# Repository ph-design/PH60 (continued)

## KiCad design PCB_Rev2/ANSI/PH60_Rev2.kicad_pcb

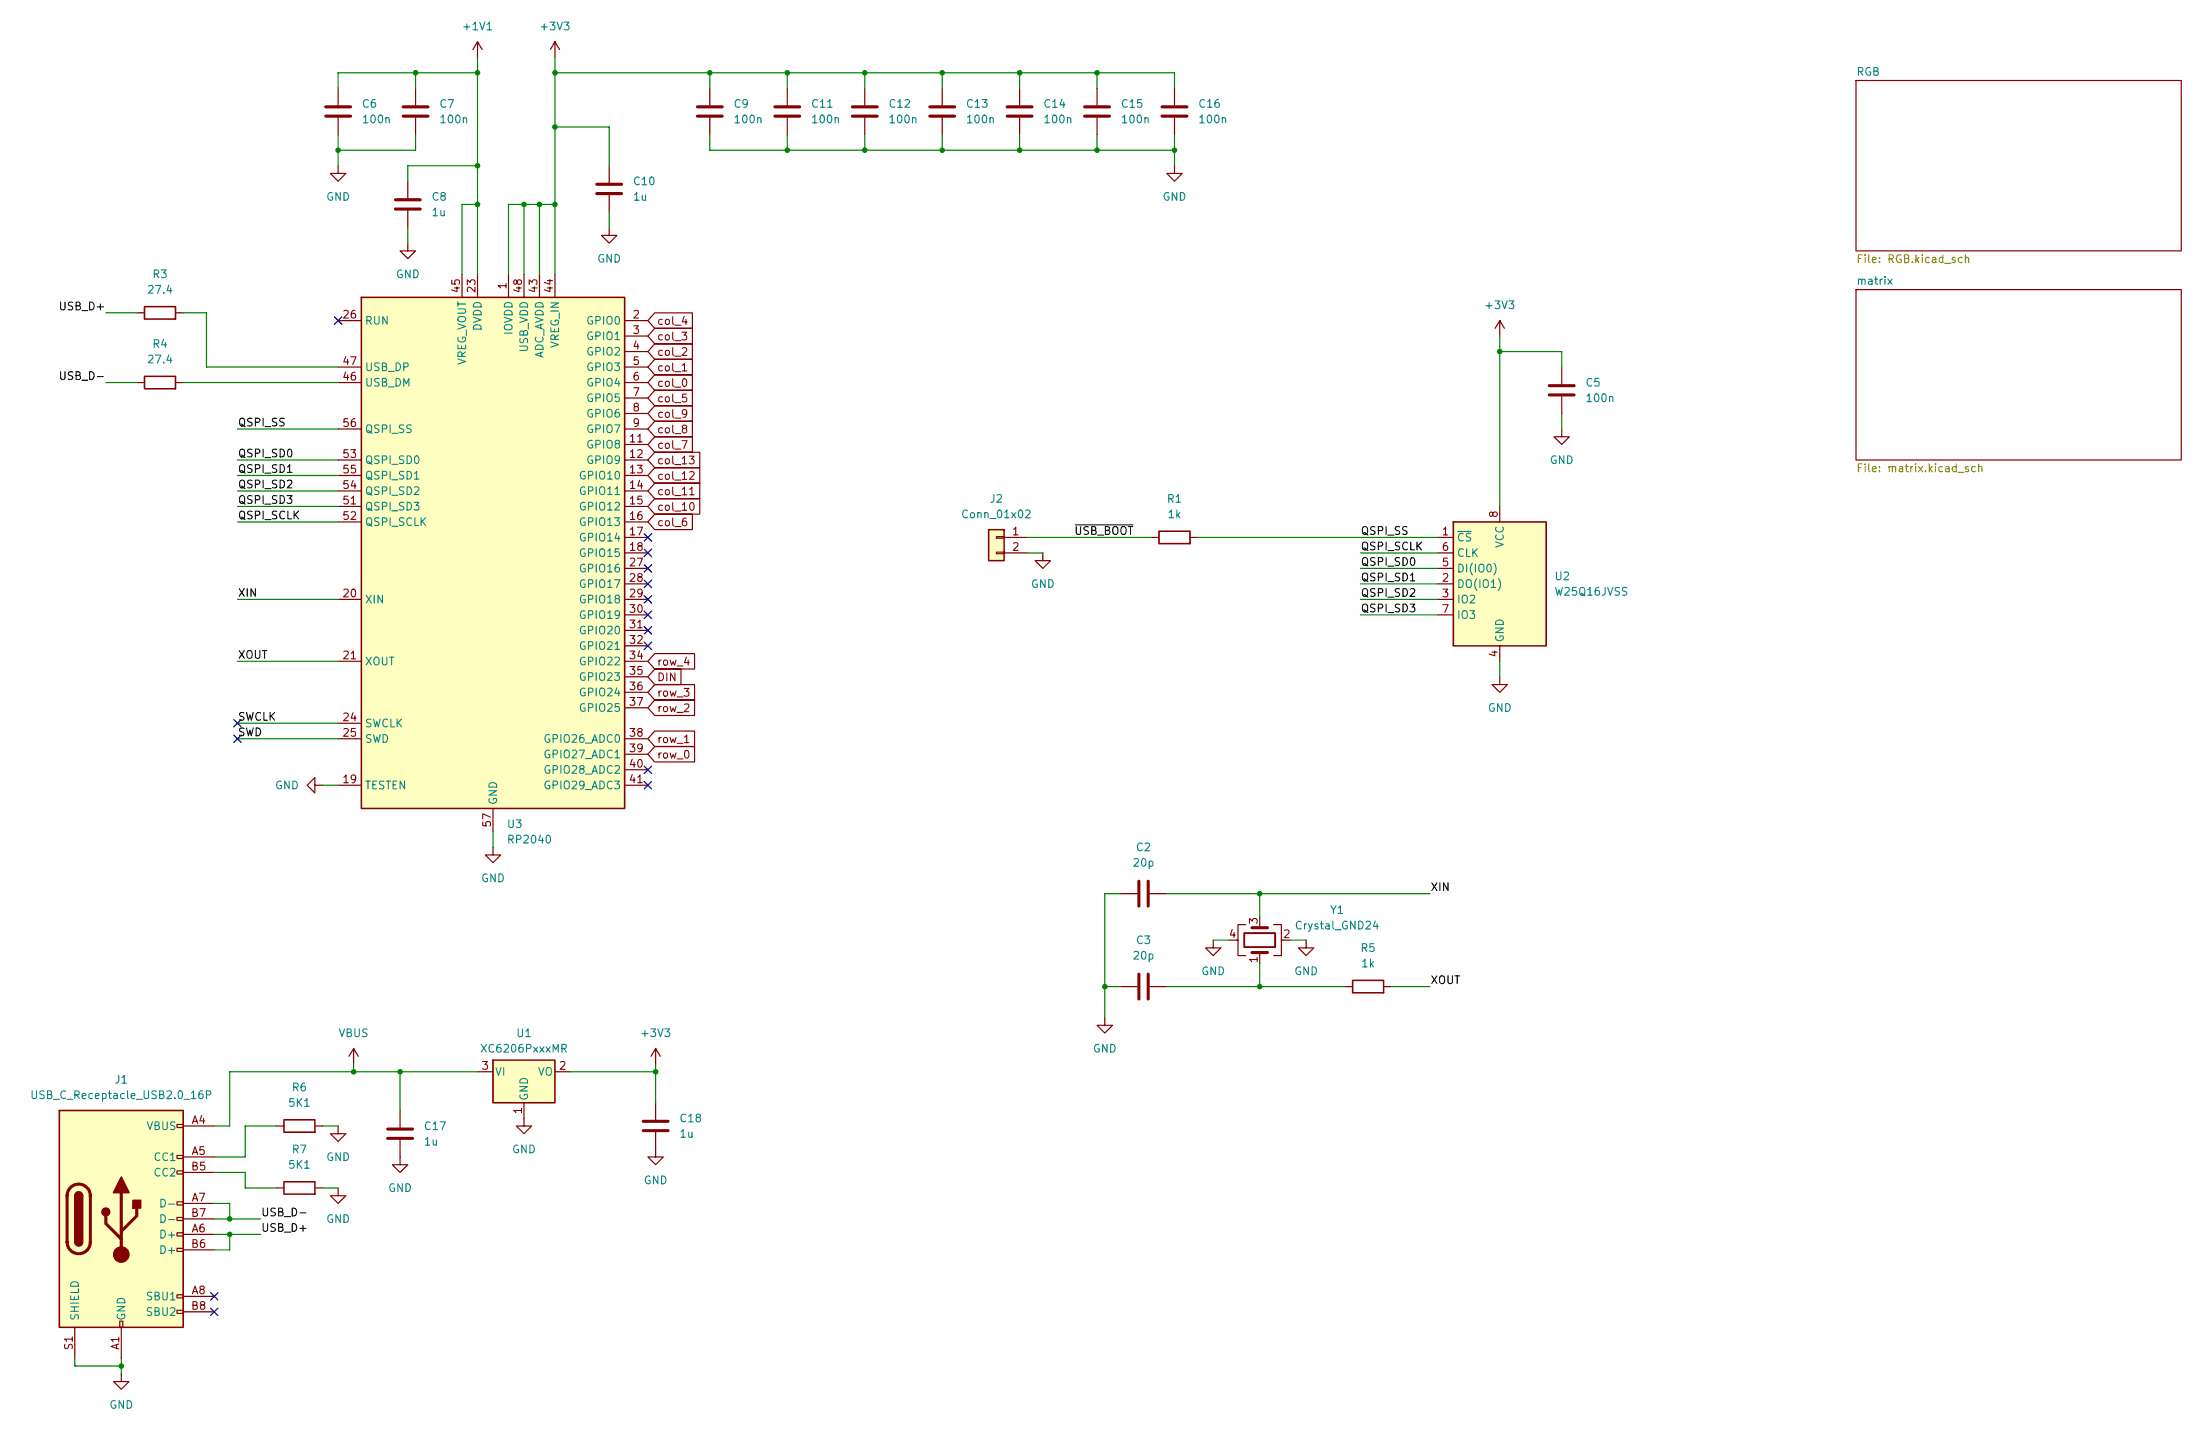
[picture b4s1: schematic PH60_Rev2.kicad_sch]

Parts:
C2, C3: 20p; C_0402_1005Metric
C5, C6, C7, C9, C11, C12, C13, C14, C15, C16: 100n; C_0402_1005Metric
C8, C10, C17, C18: 1u; C_0402_1005Metric
J1: USB_C_Receptacle_USB2.0_16P; USB_C_Receptacle_GCT_USB4105-xx-A_16P_TopMnt_Horizontal
J2: Conn_01x02; PinHeader_1x02_P2.54mm_Vertical
R1, R5: 1k; R_0402_1005Metric
R3, R4: 27.4; R_0402_1005Metric
R6, R7: 5K1; R_0402_1005Metric
U1: XC6206PxxxMR; SOT-23-3
U2: W25Q16JVSS; Winbond_USON-8-1EP_3x2mm_P0.5mm_EP0.2x1.6mm
U3: RP2040; QFN-56-1EP_7x7mm_P0.4mm_EP3.2x3.2mm_ThermalVias
Y1: Crystal_GND24; Crystal_SMD_3225-4Pin_3.2x2.5mm

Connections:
+1V1: C6.1, C7.1, C8.1, U3.23 (DVDD), U3.45 (VREG_VOUT), U3.50 (DVDD)
+3V3: C5.1, C9.1, C10.1, C11.1, C12.1, C13.1, C14.1, C15.1, C16.1, C18.1, U1.2 (VO), U2.8 (VCC), U3.1 (IOVDD), U3.10 (IOVDD), U3.22 (IOVDD), U3.33 (IOVDD), U3.42 (IOVDD), U3.43 (ADC_AVDD), U3.44 (VREG_IN), U3.48 (USB_VDD), U3.49 (IOVDD)
/QSPI_SCLK: U2.6 (CLK), U3.52 (QSPI_SCLK)
/QSPI_SD0: U2.5 (DI(IO0)), U3.53 (QSPI_SD0)
/QSPI_SD1: U2.2 (DO(IO1)), U3.55 (QSPI_SD1)
/QSPI_SD2: U2.3 (IO2), U3.54 (QSPI_SD2)
/QSPI_SD3: U2.7 (IO3), U3.51 (QSPI_SD3)
/QSPI_SS: R1.2, U2.1 (~CS), U3.56 (QSPI_SS)
/SWCLK: U3.24 (SWCLK)
/SWD: U3.25 (SWD)
/USB_D+: J1.A6 (D+), J1.B6 (D+), R3.1
/USB_D-: J1.A7 (D-), J1.B7 (D-), R4.1
/XIN: C2.1, U3.20 (XIN), Y1.3
/XOUT: R5.2, U3.21 (XOUT)
/~USB_BOOT: J2.1, R1.1
DIN: U3.35 (GPIO23); also elsewhere on the board
GND: C2.2, C3.2, C5.2, C6.2, C7.2, C8.2, C9.2, C10.2, C11.2, C12.2, C13.2, C14.2, C15.2, C16.2, C17.2, C18.2, J1.A1 (GND), J1.A12 (GND), J1.B1 (GND), J1.B12 (GND), J1.S1 (SHIELD), J2.2, R6.2, R7.2, U1.1 (GND), U2.4 (GND), U3.19 (TESTEN), U3.57 (GND), Y1.2, Y1.4; also elsewhere on the board
unnamed: C3.1, R5.1, Y1.1
unnamed: J1.A5 (CC1), R6.1
unnamed: J1.B5 (CC2), R7.1
unnamed: R4.2, U3.46 (USB_DM)
unnamed: R3.2, U3.47 (USB_DP)
VBUS: C17.1, J1.A4 (VBUS), J1.A9 (VBUS), J1.B4 (VBUS), J1.B9 (VBUS), U1.3 (VI); also elsewhere on the board
col_0: U3.6 (GPIO4); also elsewhere on the board
col_1: U3.5 (GPIO3); also elsewhere on the board
col_2: U3.4 (GPIO2); also elsewhere on the board
col_3: U3.3 (GPIO1); also elsewhere on the board
col_4: U3.2 (GPIO0); also elsewhere on the board
col_5: U3.7 (GPIO5); also elsewhere on the board
col_6: U3.16 (GPIO13); also elsewhere on the board
col_7: U3.11 (GPIO8); also elsewhere on the board
col_8: U3.9 (GPIO7); also elsewhere on the board
col_9: U3.8 (GPIO6); also elsewhere on the board
col_10: U3.15 (GPIO12); also elsewhere on the board
col_11: U3.14 (GPIO11); also elsewhere on the board
col_12: U3.13 (GPIO10); also elsewhere on the board
col_13: U3.12 (GPIO9); also elsewhere on the board
row_0: U3.39 (GPIO27_ADC1); also elsewhere on the board
row_3: U3.36 (GPIO24); also elsewhere on the board
row_4: U3.34 (GPIO22); also elsewhere on the board

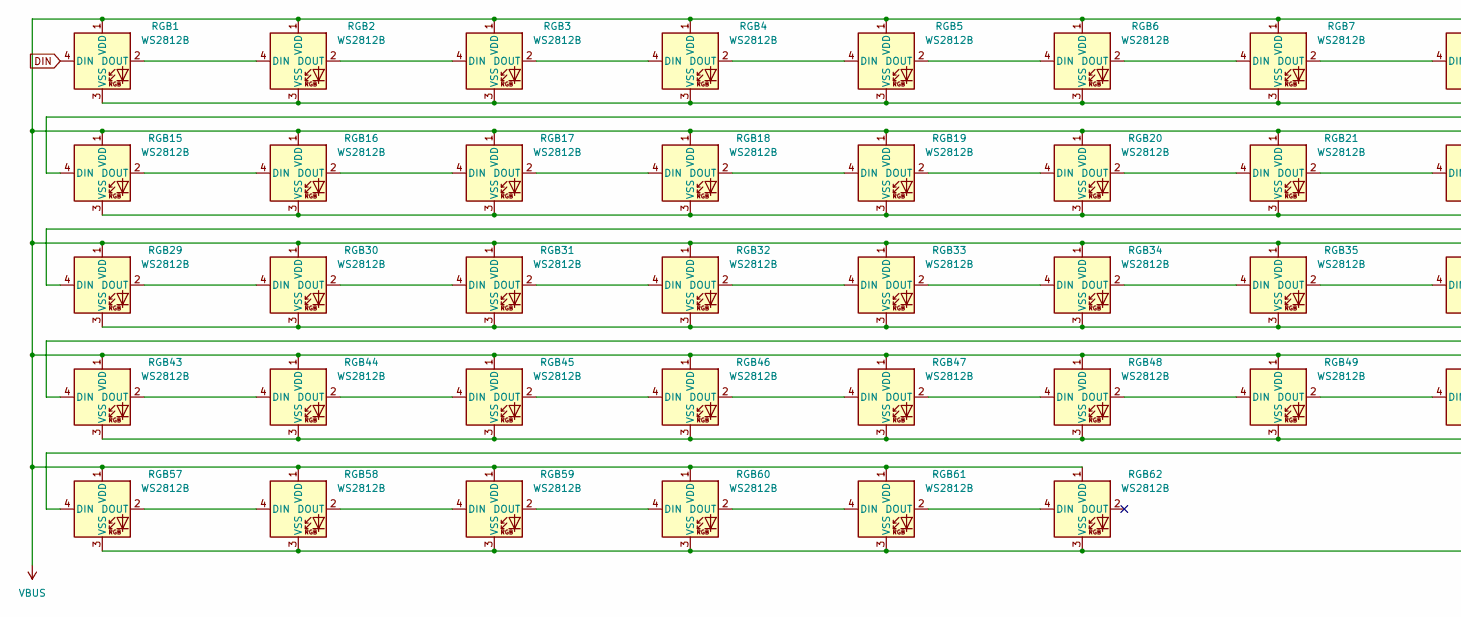
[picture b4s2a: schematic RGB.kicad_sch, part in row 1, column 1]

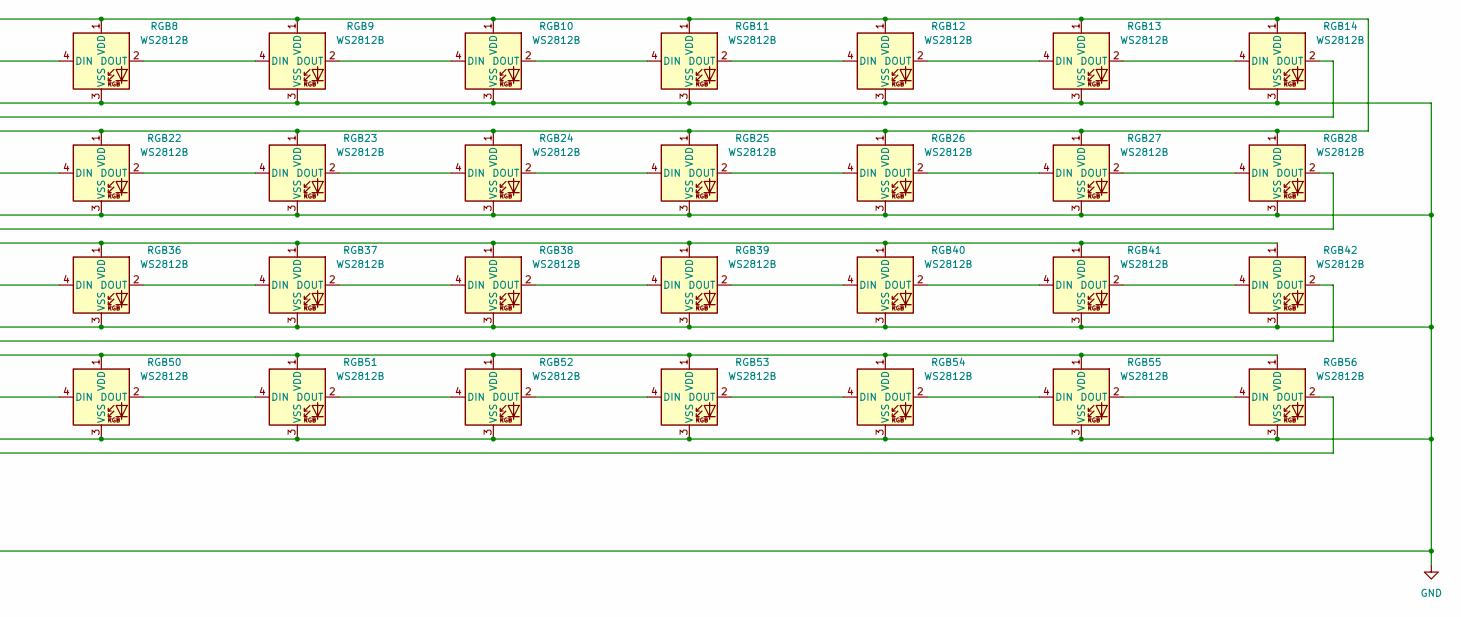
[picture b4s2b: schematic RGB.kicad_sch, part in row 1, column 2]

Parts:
RGB1, RGB2, RGB3, RGB4, RGB5, RGB6, RGB7, RGB8, RGB9, RGB10, RGB11, RGB12, RGB13, RGB14, RGB15, RGB16, RGB17, RGB18, RGB19, RGB20, RGB21, RGB22, RGB23, RGB24, RGB25, RGB26, RGB27, RGB28, RGB29, RGB30, RGB31, RGB32, RGB33, RGB34, RGB35, RGB36, RGB37, RGB38, RGB39, RGB40, RGB41, RGB42, RGB43, RGB44, RGB45, RGB46, RGB47, RGB48, RGB49, RGB50, RGB51, RGB52, RGB53, RGB54, RGB55, RGB56, RGB57, RGB58, RGB59, RGB60, RGB61, RGB62: WS2812B; ws2812B_6028

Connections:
DIN: RGB1.4 (DIN); also elsewhere on the board
GND: RGB1.3 (VSS), RGB2.3 (VSS), RGB3.3 (VSS), RGB4.3 (VSS), RGB5.3 (VSS), RGB6.3 (VSS), RGB7.3 (VSS), RGB8.3 (VSS), RGB9.3 (VSS), RGB10.3 (VSS), RGB11.3 (VSS), RGB12.3 (VSS), RGB13.3 (VSS), RGB14.3 (VSS), RGB15.3 (VSS), RGB16.3 (VSS), RGB17.3 (VSS), RGB18.3 (VSS), RGB19.3 (VSS), RGB20.3 (VSS), RGB21.3 (VSS), RGB22.3 (VSS), RGB23.3 (VSS), RGB24.3 (VSS), RGB25.3 (VSS), RGB26.3 (VSS), RGB27.3 (VSS), RGB28.3 (VSS), RGB29.3 (VSS), RGB30.3 (VSS), RGB31.3 (VSS), RGB32.3 (VSS), RGB33.3 (VSS), RGB34.3 (VSS), RGB35.3 (VSS), RGB36.3 (VSS), RGB37.3 (VSS), RGB38.3 (VSS), RGB39.3 (VSS), RGB40.3 (VSS), RGB41.3 (VSS), RGB42.3 (VSS), RGB43.3 (VSS), RGB44.3 (VSS), RGB45.3 (VSS), RGB46.3 (VSS), RGB47.3 (VSS), RGB48.3 (VSS), RGB49.3 (VSS), RGB50.3 (VSS), RGB51.3 (VSS), RGB52.3 (VSS), RGB53.3 (VSS), RGB54.3 (VSS), RGB55.3 (VSS), RGB56.3 (VSS), RGB57.3 (VSS), RGB58.3 (VSS), RGB59.3 (VSS), RGB60.3 (VSS), RGB61.3 (VSS), RGB62.3 (VSS); also elsewhere on the board
unnamed: RGB1.2 (DOUT), RGB2.4 (DIN)
unnamed: RGB2.2 (DOUT), RGB3.4 (DIN)
unnamed: RGB3.2 (DOUT), RGB4.4 (DIN)
unnamed: RGB4.2 (DOUT), RGB5.4 (DIN)
unnamed: RGB5.2 (DOUT), RGB6.4 (DIN)
unnamed: RGB6.2 (DOUT), RGB7.4 (DIN)
unnamed: RGB7.2 (DOUT), RGB8.4 (DIN)
unnamed: RGB8.2 (DOUT), RGB9.4 (DIN)
unnamed: RGB9.2 (DOUT), RGB10.4 (DIN)
unnamed: RGB10.2 (DOUT), RGB11.4 (DIN)
unnamed: RGB11.2 (DOUT), RGB12.4 (DIN)
unnamed: RGB12.2 (DOUT), RGB13.4 (DIN)
unnamed: RGB13.2 (DOUT), RGB14.4 (DIN)
unnamed: RGB14.2 (DOUT), RGB15.4 (DIN)
unnamed: RGB15.2 (DOUT), RGB16.4 (DIN)
unnamed: RGB16.2 (DOUT), RGB17.4 (DIN)
unnamed: RGB17.2 (DOUT), RGB18.4 (DIN)
unnamed: RGB18.2 (DOUT), RGB19.4 (DIN)
unnamed: RGB19.2 (DOUT), RGB20.4 (DIN)
unnamed: RGB20.2 (DOUT), RGB21.4 (DIN)
unnamed: RGB21.2 (DOUT), RGB22.4 (DIN)
unnamed: RGB22.2 (DOUT), RGB23.4 (DIN)
unnamed: RGB23.2 (DOUT), RGB24.4 (DIN)
unnamed: RGB24.2 (DOUT), RGB25.4 (DIN)
unnamed: RGB25.2 (DOUT), RGB26.4 (DIN)
unnamed: RGB26.2 (DOUT), RGB27.4 (DIN)
unnamed: RGB27.2 (DOUT), RGB28.4 (DIN)
unnamed: RGB28.2 (DOUT), RGB29.4 (DIN)
unnamed: RGB29.2 (DOUT), RGB30.4 (DIN)
unnamed: RGB30.2 (DOUT), RGB31.4 (DIN)
unnamed: RGB31.2 (DOUT), RGB32.4 (DIN)
unnamed: RGB32.2 (DOUT), RGB33.4 (DIN)
unnamed: RGB33.2 (DOUT), RGB34.4 (DIN)
unnamed: RGB34.2 (DOUT), RGB35.4 (DIN)
unnamed: RGB35.2 (DOUT), RGB36.4 (DIN)
unnamed: RGB36.2 (DOUT), RGB37.4 (DIN)
unnamed: RGB37.2 (DOUT), RGB38.4 (DIN)
unnamed: RGB38.2 (DOUT), RGB39.4 (DIN)
unnamed: RGB39.2 (DOUT), RGB40.4 (DIN)
unnamed: RGB40.2 (DOUT), RGB41.4 (DIN)
unnamed: RGB41.2 (DOUT), RGB42.4 (DIN)
unnamed: RGB42.2 (DOUT), RGB43.4 (DIN)
unnamed: RGB43.2 (DOUT), RGB44.4 (DIN)
unnamed: RGB44.2 (DOUT), RGB45.4 (DIN)
unnamed: RGB45.2 (DOUT), RGB46.4 (DIN)
unnamed: RGB46.2 (DOUT), RGB47.4 (DIN)
unnamed: RGB47.2 (DOUT), RGB48.4 (DIN)
unnamed: RGB48.2 (DOUT), RGB49.4 (DIN)
unnamed: RGB49.2 (DOUT), RGB50.4 (DIN)
unnamed: RGB50.2 (DOUT), RGB51.4 (DIN)
unnamed: RGB51.2 (DOUT), RGB52.4 (DIN)
unnamed: RGB52.2 (DOUT), RGB53.4 (DIN)
unnamed: RGB53.2 (DOUT), RGB54.4 (DIN)
unnamed: RGB54.2 (DOUT), RGB55.4 (DIN)
unnamed: RGB55.2 (DOUT), RGB56.4 (DIN)
unnamed: RGB56.2 (DOUT), RGB57.4 (DIN)
unnamed: RGB57.2 (DOUT), RGB58.4 (DIN)
unnamed: RGB58.2 (DOUT), RGB59.4 (DIN)
unnamed: RGB59.2 (DOUT), RGB60.4 (DIN)
unnamed: RGB60.2 (DOUT), RGB61.4 (DIN)
unnamed: RGB61.2 (DOUT), RGB62.4 (DIN)
VBUS: RGB1.1 (VDD), RGB2.1 (VDD), RGB3.1 (VDD), RGB4.1 (VDD), RGB5.1 (VDD), RGB6.1 (VDD), RGB7.1 (VDD), RGB8.1 (VDD), RGB9.1 (VDD), RGB10.1 (VDD), RGB11.1 (VDD), RGB12.1 (VDD), RGB13.1 (VDD), RGB14.1 (VDD), RGB15.1 (VDD), RGB16.1 (VDD), RGB17.1 (VDD), RGB18.1 (VDD), RGB19.1 (VDD), RGB20.1 (VDD), RGB21.1 (VDD), RGB22.1 (VDD), RGB23.1 (VDD), RGB24.1 (VDD), RGB25.1 (VDD), RGB26.1 (VDD), RGB27.1 (VDD), RGB28.1 (VDD), RGB29.1 (VDD), RGB30.1 (VDD), RGB31.1 (VDD), RGB32.1 (VDD), RGB33.1 (VDD), RGB34.1 (VDD), RGB35.1 (VDD), RGB36.1 (VDD), RGB37.1 (VDD), RGB38.1 (VDD), RGB39.1 (VDD), RGB40.1 (VDD), RGB41.1 (VDD), RGB42.1 (VDD), RGB43.1 (VDD), RGB44.1 (VDD), RGB45.1 (VDD), RGB46.1 (VDD), RGB47.1 (VDD), RGB48.1 (VDD), RGB49.1 (VDD), RGB50.1 (VDD), RGB51.1 (VDD), RGB52.1 (VDD), RGB53.1 (VDD), RGB54.1 (VDD), RGB55.1 (VDD), RGB56.1 (VDD), RGB57.1 (VDD), RGB58.1 (VDD), RGB59.1 (VDD), RGB60.1 (VDD), RGB61.1 (VDD), RGB62.1 (VDD); also elsewhere on the board

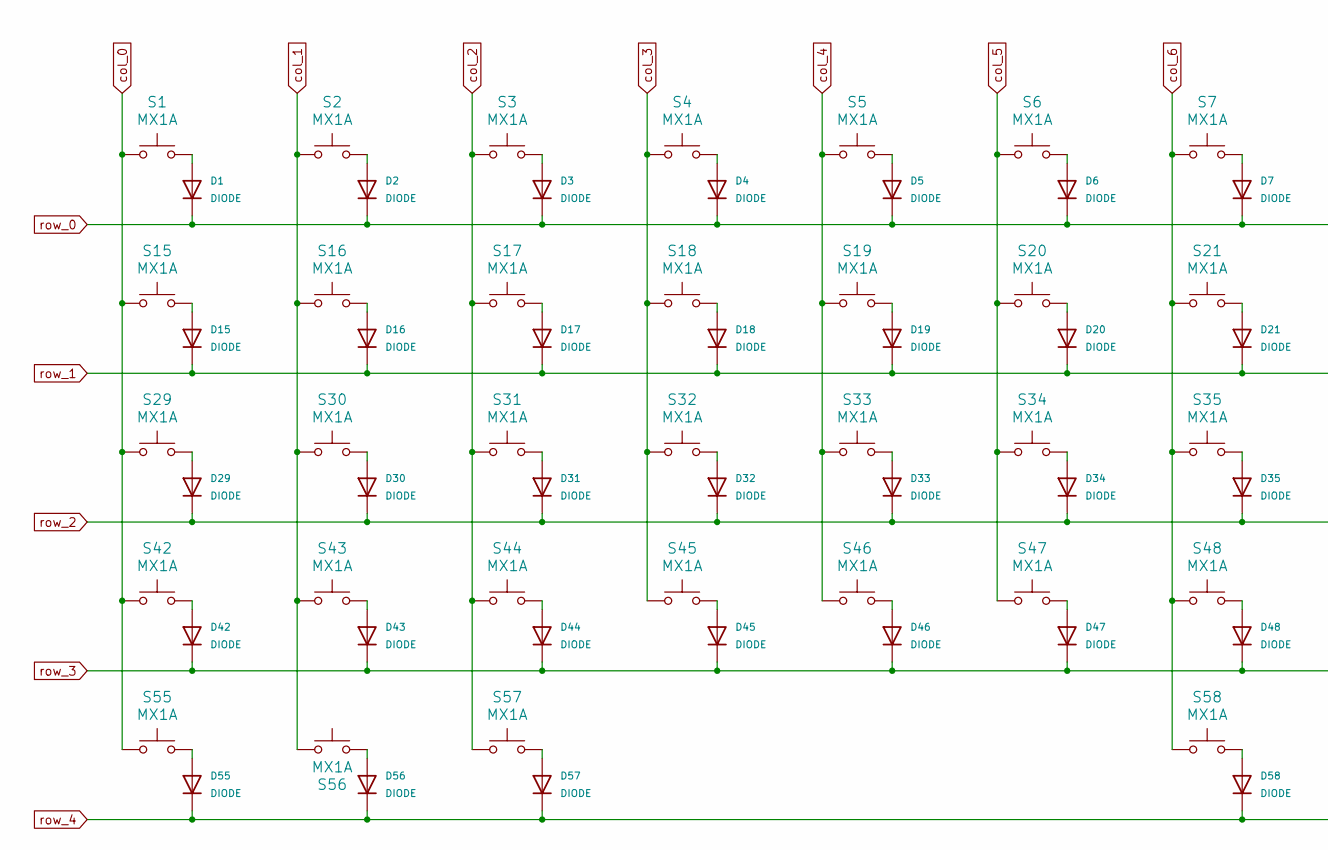
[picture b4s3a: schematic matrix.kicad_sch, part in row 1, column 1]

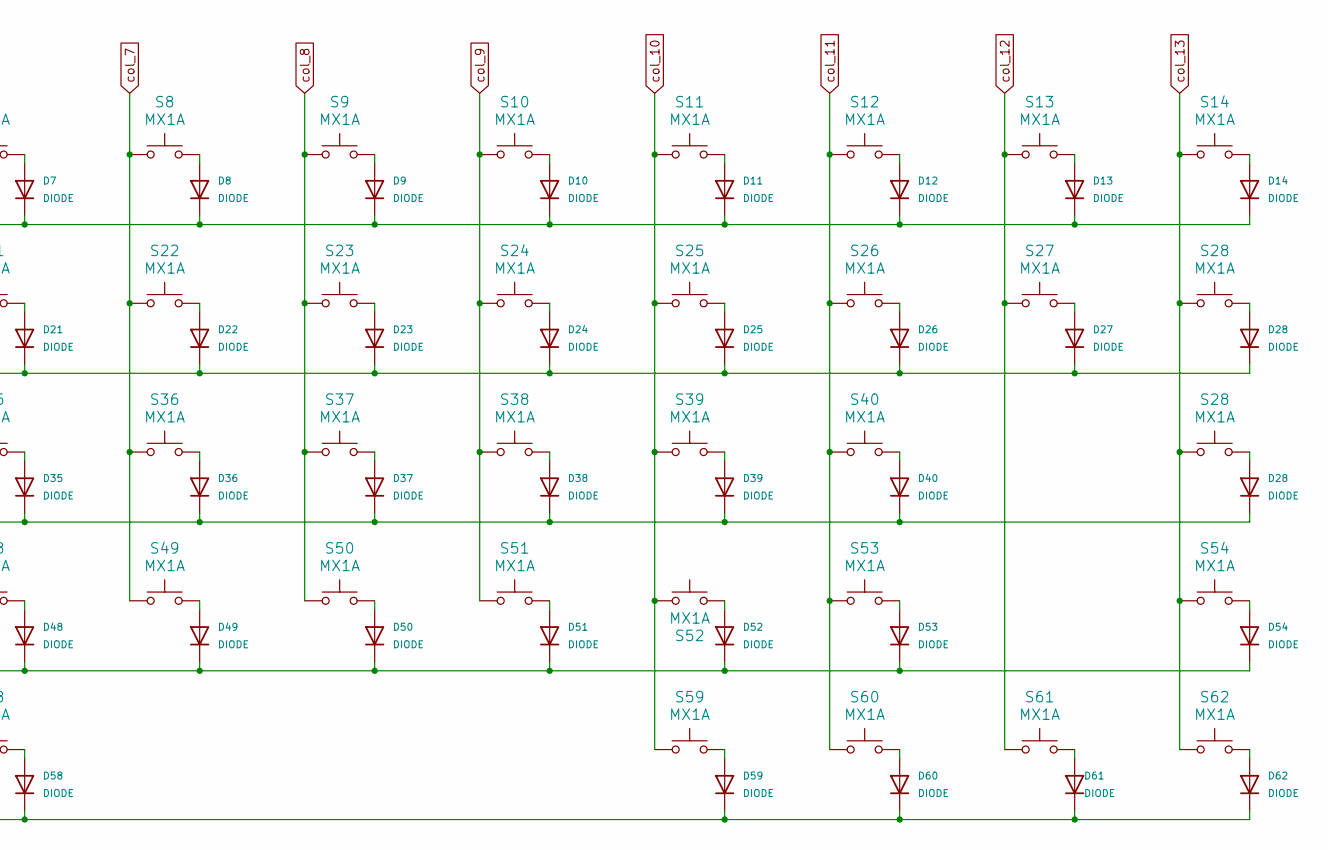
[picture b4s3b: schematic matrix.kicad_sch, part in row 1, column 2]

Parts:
D1, D2, D3, D4, D5, D6, D7, D8, D9, D10, D11, D12, D13, D14, D15, D16, D17, D18, D19, D20, D21, D22, D23, D24, D25, D26, D27, D28, D29, D30, D31, D32, D33, D34, D35, D36, D37, D38, D39, D40, D42, D43, D44, D45, D46, D47, D48, D49, D50, D51, D52, D53, D54, D55, D56, D57, D58, D59, D60, D61, D62: DIODE; D_SOD-323
S1, S2, S3, S4, S5, S6, S7, S8, S9, S10, S11, S12, S13, S16, S17, S18, S19, S20, S21, S22, S23, S24, S25, S26, S27, S30, S31, S32, S33, S34, S35, S36, S37, S38, S39, S40, S43, S44, S45, S46, S47, S48, S49, S50, S51, S52, S53: MX1A; SW_Hotswap_Kailh_MX_Plated_1.00u
S14: MX1A; SW_Hotswap_Kailh_MX_Plated_2.00u
S15: MX1A; SW_Hotswap_Kailh_MX_Plated_1.50u
S28: MX1A; SW_Hotswap_Kailh_MX_Plated_2.25u
S29: MX1A; SW_Hotswap_Kailh_MX_Plated_1.75u
S42, S55, S56, S57, S59, S60, S61, S62: MX1A; SW_Hotswap_Kailh_MX_Plated_1.25u
S54: MX1A; SW_Hotswap_Kailh_MX_Plated_2.75u
S58: MX1A; SW_Hotswap_Kailh_MX_Plated_6.25u

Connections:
unnamed: D1.2 (A), S1.1
unnamed: D2.2 (A), S2.1
unnamed: D3.2 (A), S3.1
unnamed: D4.2 (A), S4.1
unnamed: D5.2 (A), S5.1
unnamed: D6.2 (A), S6.1
unnamed: D7.2 (A), S7.1
unnamed: D8.2 (A), S8.1
unnamed: D9.2 (A), S9.1
unnamed: D10.2 (A), S10.1
unnamed: D11.2 (A), S11.1
unnamed: D12.2 (A), S12.1
unnamed: D13.2 (A), S13.1
unnamed: D14.2 (A), S14.1
unnamed: D15.2 (A), S15.1
unnamed: D16.2 (A), S16.1
unnamed: D17.2 (A), S17.1
unnamed: D18.2 (A), S18.1
unnamed: D19.2 (A), S19.1
unnamed: D20.2 (A), S20.1
unnamed: D21.2 (A), S21.1
unnamed: D22.2 (A), S22.1
unnamed: D23.2 (A), S23.1
unnamed: D24.2 (A), S24.1
unnamed: D25.2 (A), S25.1
unnamed: D26.2 (A), S26.1
unnamed: D27.2 (A), S27.1
unnamed: D28.2 (A), S28.1
unnamed: D29.2 (A), S29.1
unnamed: D30.2 (A), S30.1
unnamed: D31.2 (A), S31.1
unnamed: D32.2 (A), S32.1
unnamed: D33.2 (A), S33.1
unnamed: D34.2 (A), S34.1
unnamed: D35.2 (A), S35.1
unnamed: D36.2 (A), S36.1
unnamed: D37.2 (A), S37.1
unnamed: D38.2 (A), S38.1
unnamed: D39.2 (A), S39.1
unnamed: D40.2 (A), S40.1
unnamed: D42.2 (A), S42.1
unnamed: D43.2 (A), S43.1
unnamed: D44.2 (A), S44.1
unnamed: D45.2 (A), S45.1
unnamed: D46.2 (A), S46.1
unnamed: D47.2 (A), S47.1
unnamed: D48.2 (A), S48.1
unnamed: D49.2 (A), S49.1
unnamed: D50.2 (A), S50.1
unnamed: D51.2 (A), S51.1
unnamed: D52.2 (A), S52.1
unnamed: D53.2 (A), S53.1
unnamed: D54.2 (A), S54.1
unnamed: D55.2 (A), S55.1
unnamed: D56.2 (A), S56.1
unnamed: D57.2 (A), S57.1
unnamed: D58.2 (A), S58.1
unnamed: D59.2 (A), S59.1
unnamed: D60.2 (A), S60.1
unnamed: D61.2 (A), S61.1
unnamed: D62.2 (A), S62.1
col_0: S1.2, S15.2, S29.2, S42.2, S55.2; also elsewhere on the board
col_1: S2.2, S16.2, S30.2, S43.2, S56.2; also elsewhere on the board
col_2: S3.2, S17.2, S31.2, S44.2, S57.2; also elsewhere on the board
col_3: S4.2, S18.2, S32.2, S45.2; also elsewhere on the board
col_4: S5.2, S19.2, S33.2, S46.2; also elsewhere on the board
col_5: S6.2, S20.2, S34.2, S47.2; also elsewhere on the board
col_6: S7.2, S21.2, S35.2, S48.2, S58.2; also elsewhere on the board
col_7: S8.2, S22.2, S36.2, S49.2; also elsewhere on the board
col_8: S9.2, S23.2, S37.2, S50.2; also elsewhere on the board
col_9: S10.2, S24.2, S38.2, S51.2; also elsewhere on the board
col_10: S11.2, S25.2, S39.2, S52.2, S59.2; also elsewhere on the board
col_11: S12.2, S26.2, S40.2, S53.2, S60.2; also elsewhere on the board
col_12: S13.2, S27.2, S61.2; also elsewhere on the board
col_13: S14.2, S28.2, S54.2, S62.2; also elsewhere on the board
row_0: D1.1 (K), D2.1 (K), D3.1 (K), D4.1 (K), D5.1 (K), D6.1 (K), D7.1 (K), D8.1 (K), D9.1 (K), D10.1 (K), D11.1 (K), D12.1 (K), D13.1 (K), D14.1 (K); also elsewhere on the board
row_3: D42.1 (K), D43.1 (K), D44.1 (K), D45.1 (K), D46.1 (K), D47.1 (K), D48.1 (K), D49.1 (K), D50.1 (K), D51.1 (K), D52.1 (K), D53.1 (K), D54.1 (K); also elsewhere on the board
row_4: D55.1 (K), D56.1 (K), D57.1 (K), D58.1 (K), D59.1 (K), D60.1 (K), D61.1 (K), D62.1 (K); also elsewhere on the board

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
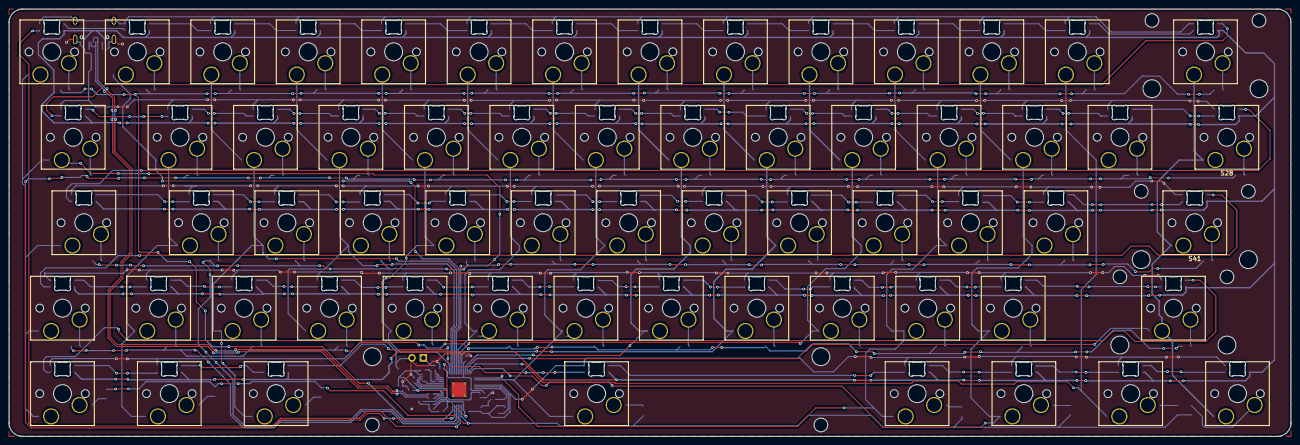
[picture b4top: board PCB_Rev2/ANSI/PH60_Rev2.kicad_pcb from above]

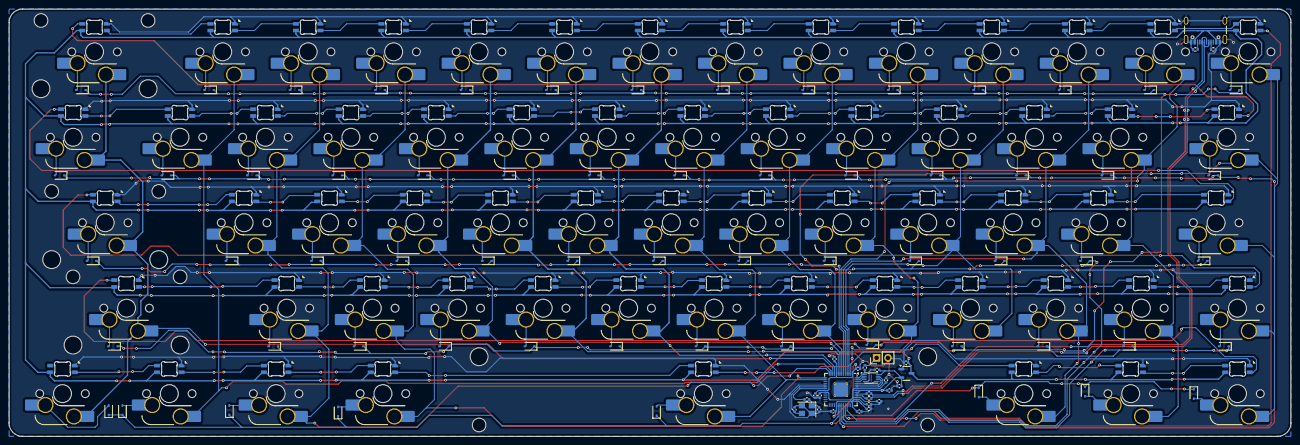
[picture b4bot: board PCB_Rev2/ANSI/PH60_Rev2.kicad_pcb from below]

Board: 2 copper layers, 285.8 x 95.2 mm, 214 parts (152 on the bottom side), 163 nets.

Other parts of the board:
D41: DIODE; D_SOD-323
S41: MX1A; SW_Hotswap_Kailh_MX_Plated_2.25u

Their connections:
unnamed: D41.2 (A), S41.1
col_13: S41.2; also elsewhere on the board

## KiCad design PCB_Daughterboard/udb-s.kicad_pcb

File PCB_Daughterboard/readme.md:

# Unified Daughterboard S Series Project

## GitHub Project
[UDB-S](https://github.com/Unified-Daughterboard/UDB-S)

## Introduction

The Unified Daughterboard Project standardizes USB daughterboards for custom mechanical keyboards. It provides a tested PCB design, ensuring easier maintenance and repair.

For more details, visit the main website.

## S Series

The S1 variant features a new form factor developed from real-world production usage and designer input.

### Features:

- **Form Factor**: "Wide and narrow" 40mm wide x 9mm deep x 1.6mm thick, avoiding common obstacles in custom keyboards. Mountable both right-side-up and upside-down.
- **Mounting Points**: 2 x M3 mounting points, reducing thread defect issues and assembly effort.
- **Sourcing**: Easy and inexpensive to source via JLCPCB or similar.
- **Design Enhancements**: Large DB corner radii allow keyboard cases to be milled at a large inner radius.
- **Protection and Shielding**: ESD protection, overcurrent protection, overvoltage protection, shielding noise decoupling, and single-path grounding to chassis functionality.
- **Connector**: New Molex Pico-EZmate Connector, replacing the JST-SH on previous versions, with 1:1 connector pinout to retain compatibility with existing PCBs.

### My Modifications

This project is based on the Unified Daughterboard S Series (UDB-S). Key modifications include:

- **Redesigned PCB**: The PCB dimensions have been altered to better fit custom keyboards.
- **Updated Slots**: The slots between the PCB and keyboard connections have been replaced to make USB-C connector more flexible.

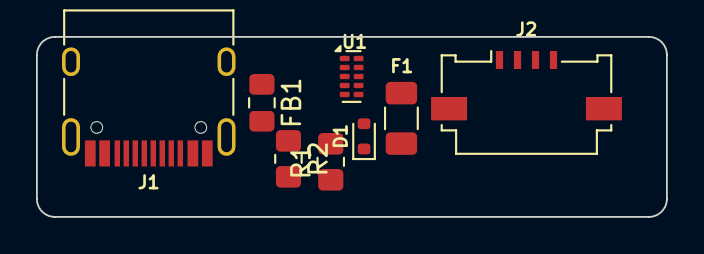
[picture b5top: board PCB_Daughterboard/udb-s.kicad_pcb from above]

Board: 4 copper layers, 35.0 x 10.0 mm, 8 parts (0 on the bottom side), 8 nets, no tracks yet.

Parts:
D1: ESD5Z5V0; D_SOD-523
F1: SMD0805-050-16V; Fuse_1206_3216Metric
FB1: GZ2012D601TF; L_0805_2012Metric_Pad1.15x1.40mm_HandSolder
J1: TYPE-C-31-M-12; USB_C_Receptacle_HRO_TYPE-C-31-M-12
J2: 200528-0040; Molex_200528-0040_1x04-1MP_P1.00mm_Horizontal
R1, R2: 5.1k; R_0805_2012Metric_Pad1.20x1.40mm_HandSolder
U1: TPD4E05U06DQAR; USON-10_2.5x1.0mm_P0.5mm

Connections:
5V: F1.2, J2.1
D+: J1.A6 (D+), J1.B6 (D+), J2.3, U1.4 (D2+), U1.5 (D2-), U1.6 (NC), U1.7 (NC)
D-: J1.A7 (D-), J1.B7 (D-), J2.2, U1.1 (IO1), U1.2 (IO2), U1.9 (NC), U1.10 (NC)
GND: D1.2 (A2), FB1.2, J1.A1 (GND), J1.A12 (GND), J1.B1 (GND), J1.B12 (GND), J2.4, J2.MP (MountPin), R1.1, R2.2, U1.3 (GND), U1.8 (GND)
GNDPWR: FB1.1, J1.S1 (SHIELD)
unnamed: J1.A5 (CC1), R1.2
unnamed: J1.B5 (CC2), R2.1
VBUS: D1.1 (A1), F1.1, J1.A4 (VBUS), J1.A9 (VBUS), J1.B4 (VBUS), J1.B9 (VBUS)

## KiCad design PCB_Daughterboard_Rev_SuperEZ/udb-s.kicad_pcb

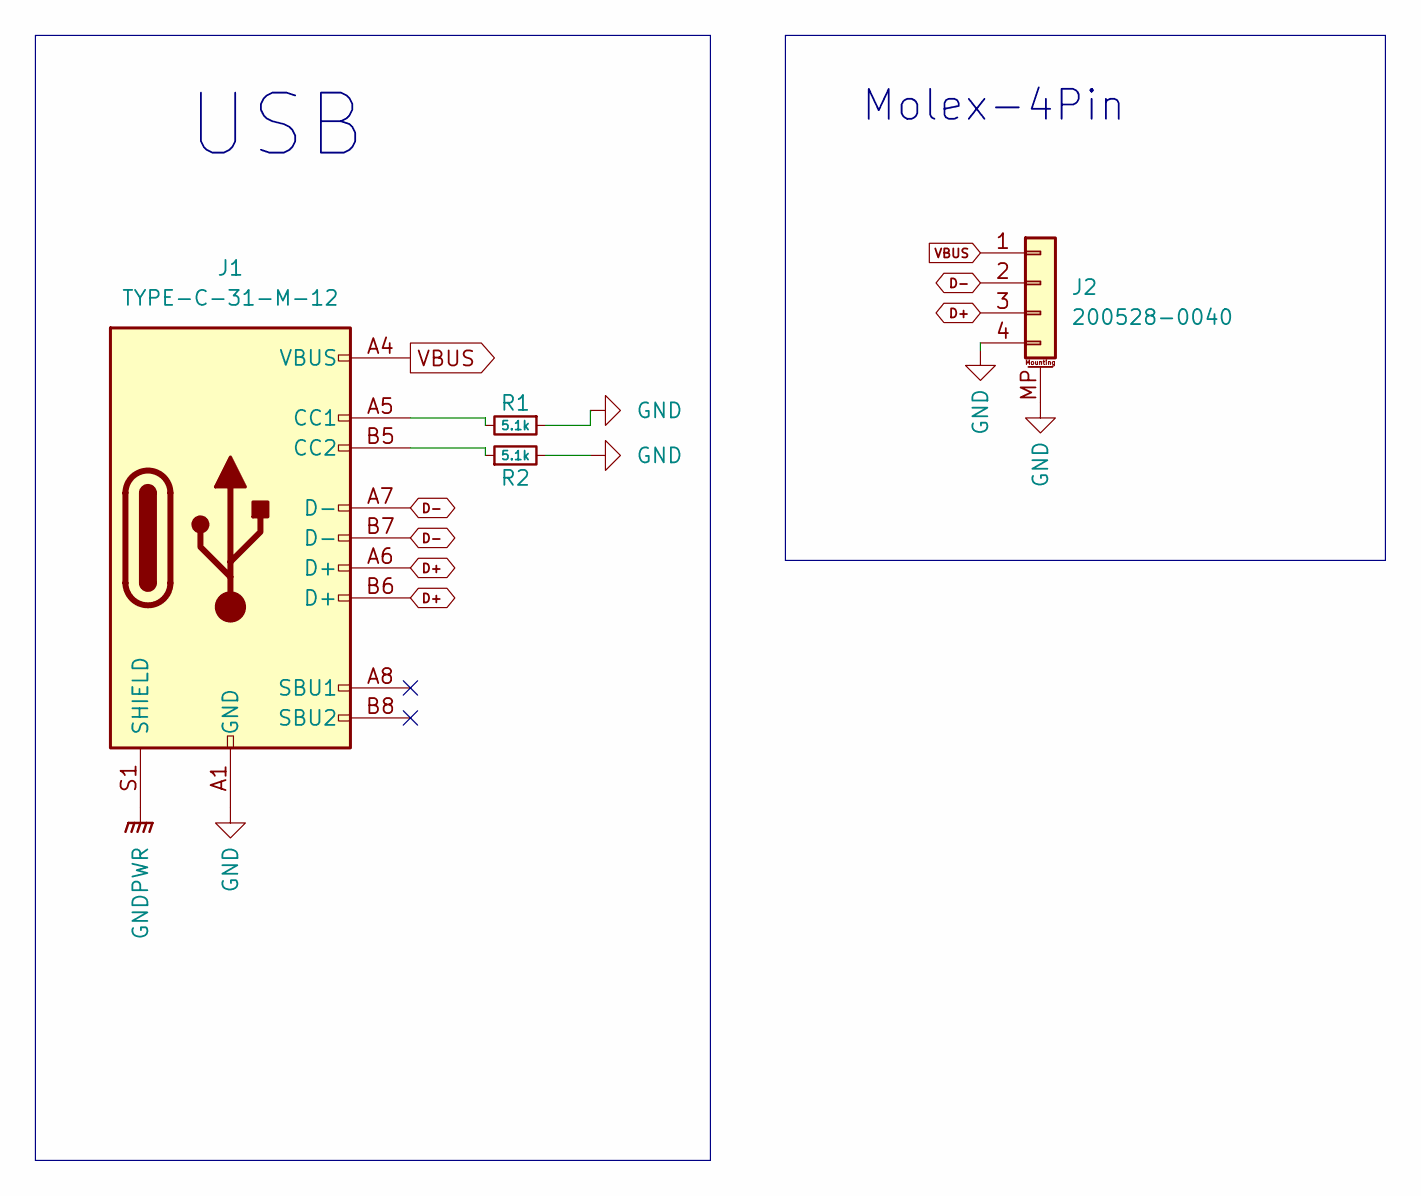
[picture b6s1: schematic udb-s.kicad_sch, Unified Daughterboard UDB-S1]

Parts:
J1: TYPE-C-31-M-12; USB_C_Receptacle_HRO_TYPE-C-31-M-12; Manufacturer Part Number TYPE-C-31-M-12; LCSC Part Number C165948
J2: 200528-0040; Molex_200528-0040_1x04-1MP_P1.00mm_Horizontal; Manufacturer Part Number 78171-0004; LCSC Part Number C588524
R1, R2: 5.1k; R_0805_2012Metric_Pad1.20x1.40mm_HandSolder

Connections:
D+: J1.A6 (D+), J1.B6 (D+), J2.3
D-: J1.A7 (D-), J1.B7 (D-), J2.2
GND: J1.A1 (GND), J1.A12 (GND), J1.B1 (GND), J1.B12 (GND), J2.4, J2.MP (MountPin), R1.1, R2.2
GNDPWR: J1.S1 (SHIELD)
unnamed: J1.A5 (CC1), R1.2
unnamed: J1.B5 (CC2), R2.1
VBUS: J1.A4 (VBUS), J1.A9 (VBUS), J1.B4 (VBUS), J1.B9 (VBUS), J2.1

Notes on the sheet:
USB
Molex-4Pin

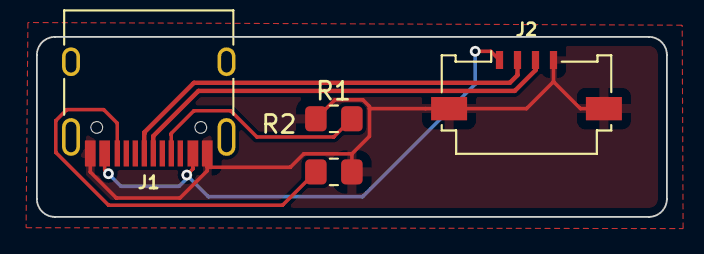
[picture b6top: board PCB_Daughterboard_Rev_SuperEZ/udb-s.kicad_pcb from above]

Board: 2 copper layers, 35.0 x 10.0 mm, 4 parts (0 on the bottom side), 6 nets.

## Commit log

2024-07-10 Update LICENSE
2024-07-10 add lib
2024-07-10 update 3d printing model
2024-07-10 update per model step file
2024-07-10 sch and pcb
2024-07-10 UPDATE PCB
2024-07-11 Replaced footprints
    Replaced some footprints that were unused or wrong with properly modified KiCAD default footprints
2024-07-11 Remodel whole system to nrfmicro
2024-07-11 PCB Updates
2024-07-14 Rename
2024-07-14 PCB wiring and 3D model generation
2024-07-14 Add Daughterboard
2024-07-14 Updated to Rev 2
2024-07-15 Routing
2024-07-15 PCB Update
    Finished the wiring of PCB
2024-07-15 PCB Copper Filling
2024-07-15 PCB Edge Rounding
2024-07-15 PCB Modifying and 3D Model Generating
2024-07-15 PCB Optimization
2024-07-16 Update daughterboard to adapt keyboard
2024-07-16 Add 3D model
    Not complete yet
2024-07-17 Update daughterboard 3d model
2024-07-17 Add production files
    Not complete yet.
2024-07-21 Add BOM
    Maybe complete
2024-07-22 BOM modify rev2
    New SOD-123 replaced old 0804 for diode.
2024-07-22 Modify pos and bom
2024-07-22 update 3D model
    daughterboard
2024-07-23 Add a demo daughterboard & update gerber flies
2024-08-04 add case_mode_rev3
2024-08-15 Wiring Fixing
2024-08-24 Rev3 start and project modify
2024-08-24 Update PCB Rev3
2024-08-24 modify routing
2024-08-31 PCB Rev3 Layout
2024-09-09 Add Multi-Keymap Support
2024-09-09 Generate Gerber Files
2024-09-10 PCB Re-Layout
2024-09-13 Add RGB Lighting for PCB Rev3
2024-09-28 Typo changes.
2024-09-28 Create README-zh_CN
    Add multi language support.
2024-09-28 Update README.md
    Add multi language support.
2024-10-16 Create .gitignore
    Ignore all the backup file.
    (I think it should only be locally)
2024-10-16 Rename and delete all the backup file in repository.
2024-10-19 Rev.0 publish.
    Though it's not mean something.
2024-10-19 Rev.1 release.
    Our first useable keyboard.
2024-10-22 Huge project structure update.
    For the better project structure, We turned all versions backwards one version number. From this version, the main branch will no longer provide production files, it will be provided in the every sin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
2024-10-25 Change LDO to XC6206
    It must be work...
2024-10-25 Adjust margin to line distance.
2024-11-01 COL wired.
    ROW wires not done.
2024-11-03 ROW wired.
    Rev.2 ANSI almost done.
2024-11-03 optimize wiring.
    Better grounding performance
2024-11-03 Optimize wiring and production file.
2024-11-03 Project structure improvement.
2024-11-11 add case_rev2
2024-11-17 LDO Modification
2024-11-17 Add Stepped Caps Lock Support
2024-11-21 Add GH60 Mounting
2024-11-21 Update Multi PCB Model
2024-11-21 Add GND Through Hole for Crystal
2024-11-21 Wiring Improvement
2024-11-21 Tinkering
2024-11-21 Change the Direction of Bottom Keys
2024-11-25 Add left shift 64 plate draft file
2024-11-25 Add ISO Support
2024-11-25 Package Modification
2024-11-25 Wiring and Ground Connection Improvement
2024-11-26 Add LC52810 RF Module
2024-11-26 Schematic Tinkering and RF Module Placing
2024-11-28 add latest model file
2024-11-28 Rev.2 release!
    Needs more works to do still...
2024-11-28 Switching to the newest branch and add warning.
2024-12-03 Rev3.init().;
    Change ws2812b footprint.
    More GND hole.
    More things to do...
2024-12-04 Wiring and Placing Improvement
2024-12-05 Multi PCB Rework
2024-12-05 Multi PCB Wiring
2024-12-05 Tinkering of Multi PCB
2024-12-05 Multi PCB Production File Generation
2024-12-05 Ground Plane Continuity Improvement
2024-12-05 Optimized pretty.
2024-12-05 Wires optimization.
    More GND hole still needed...
2024-12-06 PCB Wiring Enhancement
2024-12-06 PCB Production File Generation
2024-12-06 Add QMK logo for mask.
2024-12-07 PCB Silkscreen Rearrangement
2024-12-08 Better wiring.
2024-12-09 Adjust the Capacitance of LDO Input/Output Capacitor
2024-12-09 Add Production files.
2024-12-09 Swap the Place of S42 and S14-2 on the PCB
2024-12-11 PCB Tinkering
2024-12-12 Adjust Switch Direction
2024-12-16 QFN-56 Thermal Via Redesign
2024-12-17 Production Files Generation
2024-12-20 PCB Wiring Update
2024-12-22 Add jlc production file.
2025-01-16 Wiring Rearrangement
2025-02-20 Mounting hole improvement and ESD protection
2025-02-20 Solder Mask Adjustment
2025-03-10 Update PCB Routing
2025-03-25 Remove Diode Silkscreen
2025-03-27 PCB Mask Modification
2025-03-27 Initial commit.
2025-03-31 Add Low Profile PCB
2025-04-03 Route RGB light.
2025-04-04 [WIP] Route all lights
2025-04-05 Add another RGB footprint.
2025-04-05 Almost route done.
2025-04-05 Change RGB footprint
2025-04-08 Add mounting hole.
2025-04-14 Change fuse to 0603 for better performance
2025-04-14 Update ws2812B_6028_FIX.kicad_mod
    Better for SMT
2025-04-14 Add hole for stabilizer.
2025-04-15 Board Edge Cut Fix
2025-04-27 Recalculate USB resistor.
2025-04-27 Hole Update.
2025-04-28 Project structure and readme update.
2025-08-17 Merged form Rev2
2025-08-17 Add plates via submodule
2025-08-17 Add wireless part
2025-08-18 Finish board design
2025-08-18 Regroup
2025-08-21 Add mounting hole
2025-08-21 Antenna update
2025-08-22 DRC checked
2025-09-08 Production test
2025-09-26 More stabilization circuit
2025-09-26 vbus layout
2025-09-30 12
    12
2025-09-30 drc 二次
    gnd过孔摆放较随意，后续可优化
2025-09-30 丝印布局（未检查）
    1
2025-10-02 drc三次
    元件部分layout，移动一个电容，新增0f调试电容，电源轨修改
2025-10-04 过孔优化，部分走线调整
    1
2025-10-08 四次drc
    gnd过孔精简，3v3添加0F调试电容
2025-10-10 Routing update
2025-10-10 drc确认
    1
2025-10-18 1
    1
2025-10-18 泪滴添加
    1
2025-10-24 1
    11
2025-10-27 3v3电源修改
    1
2025-10-27 Update net routing and via placements in PH60_Rev3.kicad_pcb
    Refactored and optimized net 1, 138, 139, 140, and 150 routing, including the addition, removal, and adjustment of several segments and vias. Improved clarity and connectivity for key nets, especiall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
2025-11-02 开关逻辑修改
    取消开关接地，加入二极管以及mos管，注意：mos管封装引脚有修改
2025-11-02 Initial commit
    # Initial commit
    + Add 7u-space-bar HHKB layout plate and outer case.
    + Adjust plate mounting slot for HHKB plate.
    + Add flat switch for non-PH60W PCB.
2025-11-04 Improve PCB compatibility
    + Add a clip on both side of the case to prevent potential offset.
    + Raise the inner-height of the case for 1mm to improve compatibility for other tri-mode PCBs.
    + Slight adjustment to flat switch.
2025-11-04 Fix HHKB plate stabilizer issue
2025-11-04 Add rev3 LS64 plate
2025-11-05 添加rev3_A文件夹
    将锂电管理芯片替换成LGS5500
2025-11-05 REV3 与 REV3_A 合并
2025-11-05 Fix LS64 plate issue
2025-11-06 Optimized seams
    slightly optimized the seams around the left side-case and two switches
2025-11-13 New project creation
2025-11-16 Integrated to Rev3
2025-11-18 Add LS64 plate for PTG PCB
    + Add LS64 plate for PTG PCB
    + Fix a HHKB plate issue
    + Update Readme
2025-11-18 Add WinKey plate
    + Add a WK plate supports both normal and stepped capslock
2025-11-20 muliti layout
2025-11-20 layout
2025-11-21 With the basic layout and wiring completed, a simple DRC (Digital Router Control) process is performed.
    There is an issue with the satellite axis position that needs to be addressed, and there is also an issue with some pad overlap that needs to be resolved.
2025-11-24 Add more split space
2025-11-26 drc and pcb layout
2025-11-26 over
2025-11-26 drc and layout
2025-12-02 Add H60EC plate
2025-12-02 Add split outer cases
    + Add 256mm split HHKB and normal outer cases. Thanks to @sneer2ev1
    + Fix a typo issue in readme
2025-12-03 layout
    原件调整
2025-12-03 layout and drc
    简单完成基础布局及走线，drc‘完成，未经审核
2025-12-04 muliti布局调整校对
    usb差分对需要评估，调整C18和C19电容布局，调整部分走线间距，铺设部分gnd过孔
2025-12-11 Change charger and power supply
2025-12-12 供电原理图审查
2025-12-12 Replace cap
2025-12-12 部分引脚修改，简单drc，天线部分与原件与dre元件位置修改
2025-12-12 上传遗漏
2025-12-12 mcu走线间距线宽调整至0.15mm，vbus与vddout滤波电容布局调整
2025-12-12 放置部分gnd过孔
2025-12-12 DRC check
2025-12-13 Wires change
2025-12-13 multi电池段子位置调整
2025-12-13 Update holder design for Multi PCB
2025-12-14 Wires update
2025-12-15 mcu核心布局修改，轴走线间距调整
2025-12-15 DRC checked X2
2025-12-15 删除一个gnd
2025-12-15 二极管位置修改，pcb全局审核
2025-12-16 Update plate_iso.step
    + Add support for stepped capslock
2025-12-16 Add 6u HHKB and WKL layout
    + Add 6u HHKB plate and top case
    + Add split 6u HHKB top case
    + Rename HHKB to HHKB 7u
    + Fix 6u HHKB Plate issue
2025-12-16 Fix split space and remove 6U HHKB
2025-12-17 6u空格添加，卫星轴修改
2025-12-20 Add split backspace & rshift plate
2025-12-24 Redesign antenna and space switch
2025-12-25 multi天线过孔调整，审核
2025-12-25 Modify silkscreen
2025-12-30 Add ANSI Split rShift + Spacebar plate
    Spacebar: 2.25+1.25+2.75
2026-01-01 Add non-shift 63 plate
2026-01-02 Add HHKB 7u with non-split backspace and ANSI split rshift backspace space plate
2026-01-08 Add WK split backspace plate
2026-03-20 multi v3 电感调整
2026-03-21 Change inductor position
2026-04-19 Project structure update & clean
2026-04-19 Update to kicad 10
2026-04-19 Add production file for r3 multi
2026-04-19 Initial commit for PH60 Rev.3
2026-05-30 Update inner_case_left.step
    Remove slot for power switch
